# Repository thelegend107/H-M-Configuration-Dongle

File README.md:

# Windows Network Config Dongle
Code Deploy

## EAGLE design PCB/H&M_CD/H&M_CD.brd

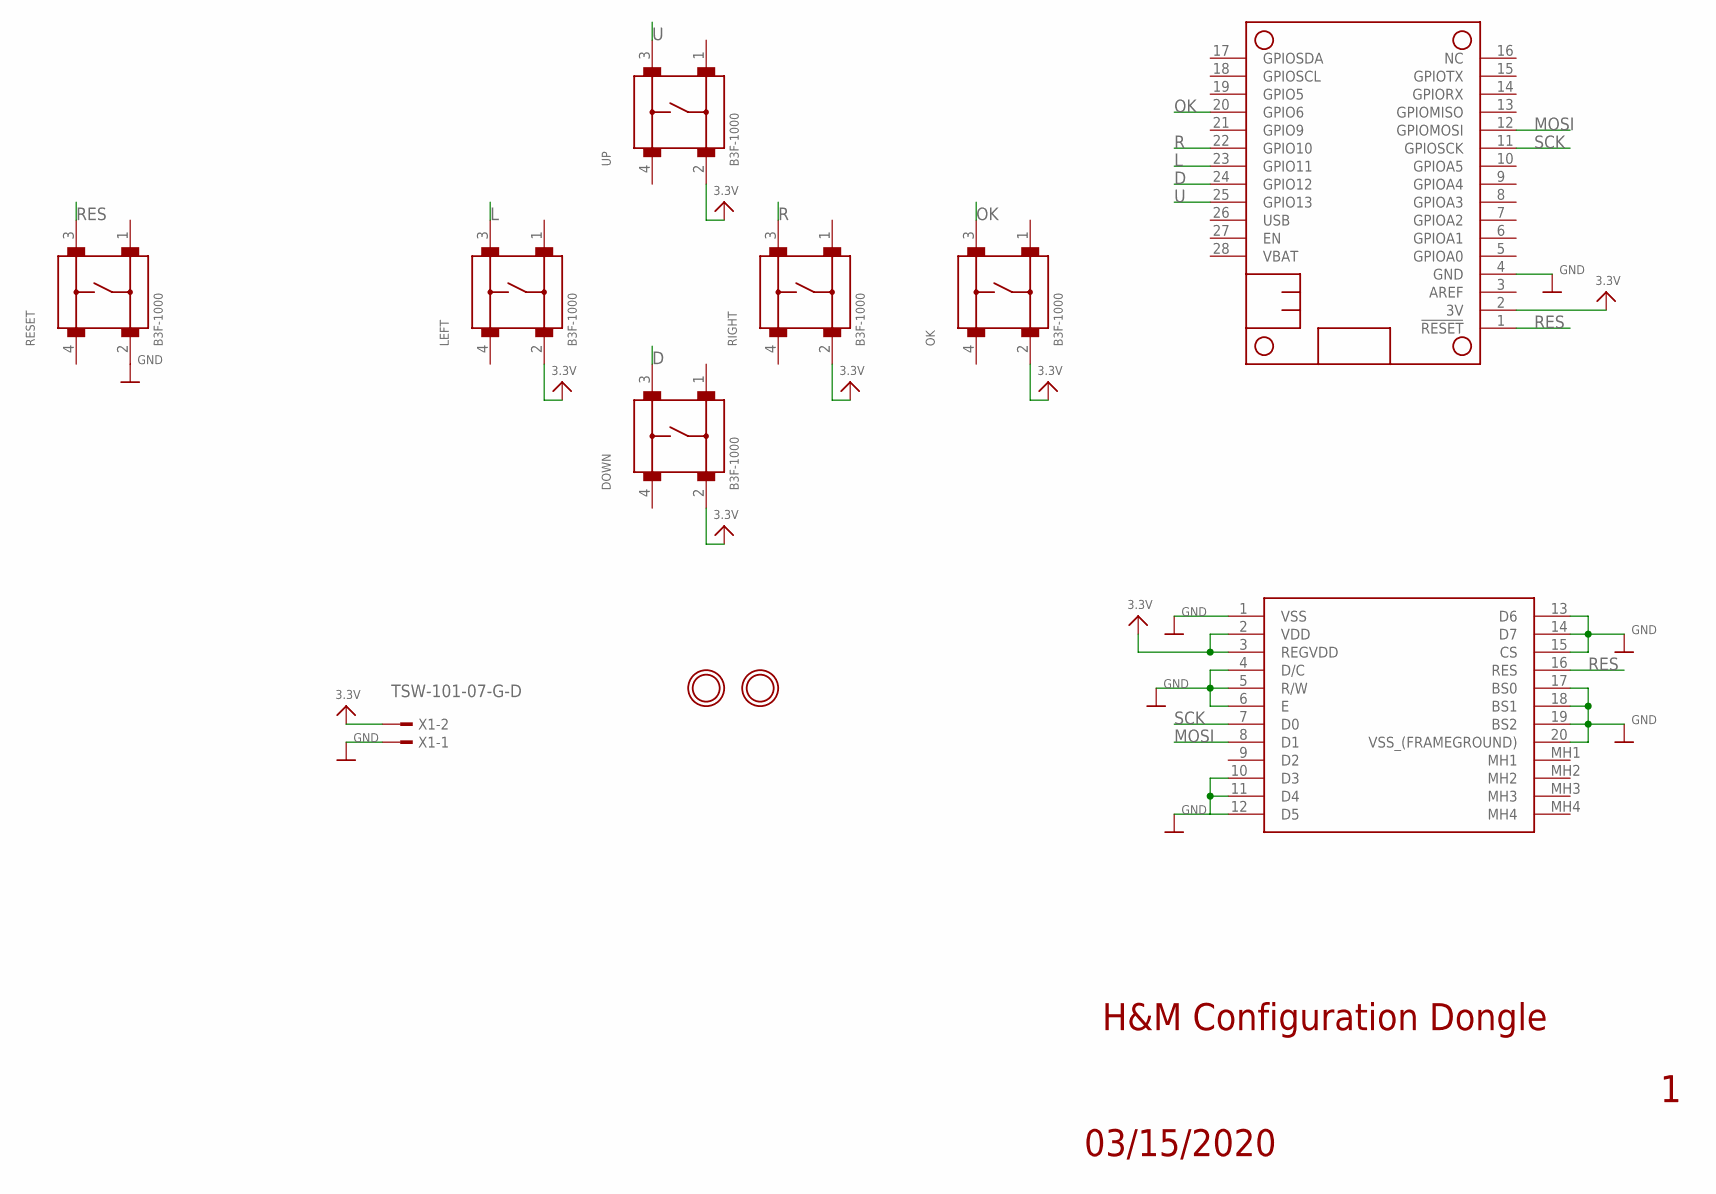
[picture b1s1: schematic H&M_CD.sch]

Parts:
20X4OLED: NHD-0420CW-AW3; NHD0420CWAW3
ATSAMD21M0: FEATHERWING_NODIM; FEATHERWING_DIM
DOWN: B3F-1000
LEFT: B3F-1000
OK: B3F-1000
RESET: B3F-1000
RIGHT: B3F-1000
U$15, U$16: MOUNTINGHOLE2.5; MOUNTINGHOLE_2.5_PLATED
UP: B3F-1000
X1: TSW-101-07-G-D; TSW-101-XX-G-D

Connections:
3.3V: 20X4OLED.2 (VDD), 20X4OLED.3 (REGVDD), ATSAMD21M0.2 (3V), DOWN.2, LEFT.2, OK.2, RIGHT.2, UP.2, X1.2
D: ATSAMD21M0.24 (GPIO12), DOWN.3
GND: 20X4OLED.1 (VSS), 20X4OLED.4 (D/C), 20X4OLED.5 (R/W), 20X4OLED.6 (E), 20X4OLED.10 (D3), 20X4OLED.11 (D4), 20X4OLED.12 (D5), 20X4OLED.13 (D6), 20X4OLED.14 (D7), 20X4OLED.15 (CS), 20X4OLED.17 (BS0), 20X4OLED.18 (BS1), 20X4OLED.19 (BS2), 20X4OLED.20 (VSS_(FRAMEGROUND)), ATSAMD21M0.4 (GND), RESET.2, X1.1
L: ATSAMD21M0.23 (GPIO11), LEFT.3
MOSI: 20X4OLED.8 (D1), ATSAMD21M0.12 (GPIOMOSI)
OK: ATSAMD21M0.20 (GPIO6), OK.3
R: ATSAMD21M0.22 (GPIO10), RIGHT.3
RES: 20X4OLED.16 (RES), ATSAMD21M0.1 (!RESET), RESET.3
SCK: 20X4OLED.7 (D0), ATSAMD21M0.11 (GPIOSCK)
U: ATSAMD21M0.25 (GPIO13), UP.3

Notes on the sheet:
03/15/2020
H&M Configuration Dongle

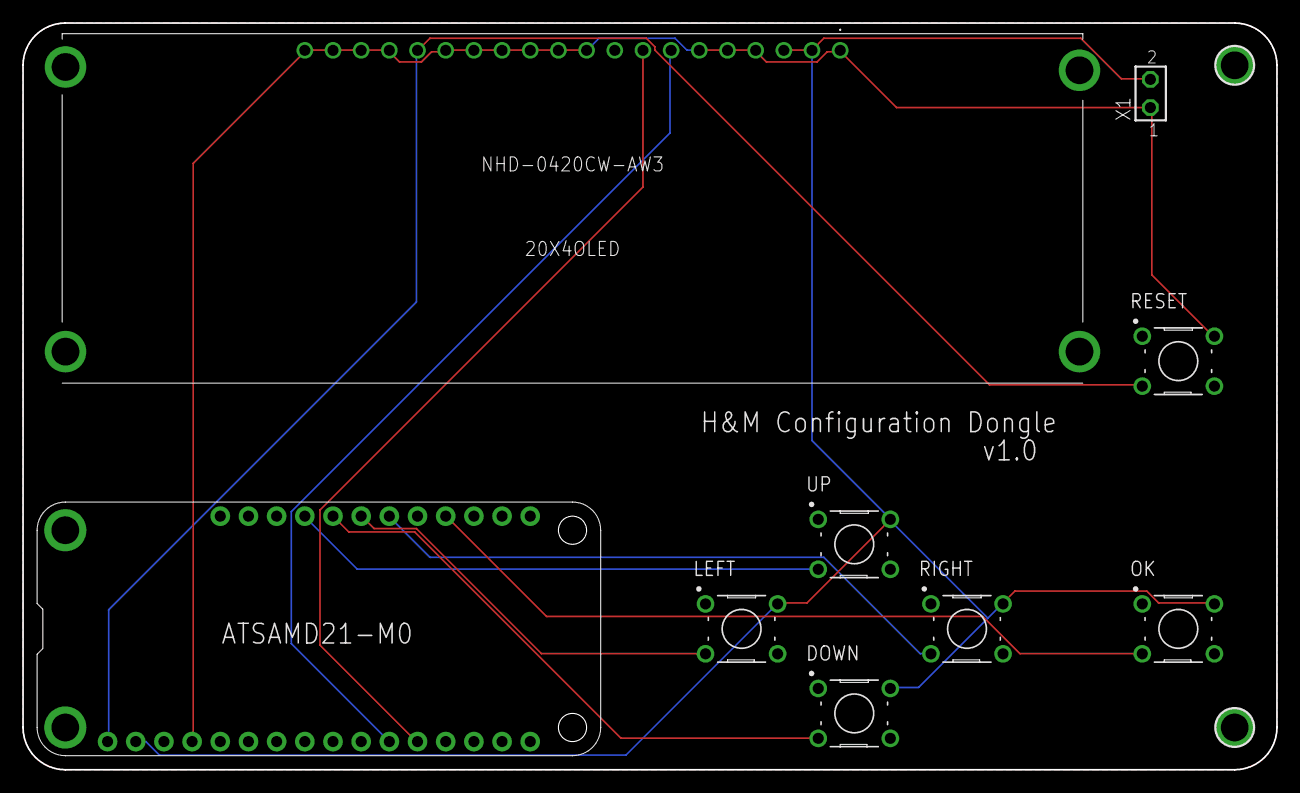
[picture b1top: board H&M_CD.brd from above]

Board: 2 copper layers, 113.0 x 67.3 mm, 11 parts (0 on the bottom side), 10 nets.

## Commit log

2021-12-26 project
2021-12-26 ardunio project
2021-12-26 project pt.3

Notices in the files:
parts and their libraries:
microbuilder: This work is placed in the public domain, and may be freely used for commercial and non-commercial work with the following conditions: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
